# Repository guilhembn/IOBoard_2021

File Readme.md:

# IO board Eurobot 2021

## Protobuf

For the fist time you try to build protobuf files, you need to run `setups.sh` in EmbeddedProto:

`cd software/lib/EmbeddedProto`
`./setup.sh`

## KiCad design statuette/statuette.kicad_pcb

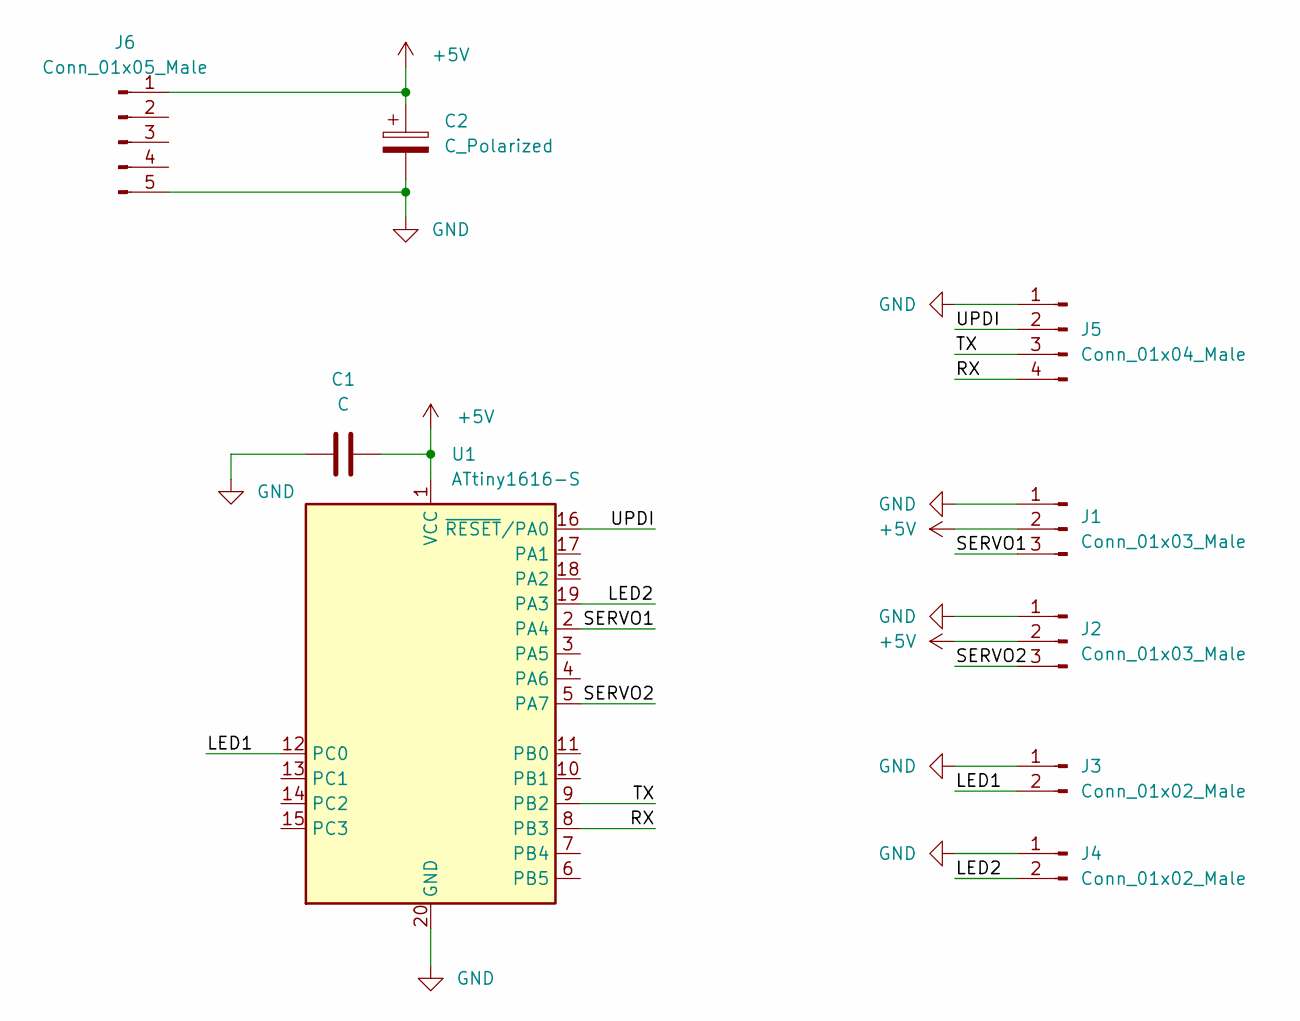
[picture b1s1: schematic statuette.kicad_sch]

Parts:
C1: C; C_0603_1608Metric_Pad1.08x0.95mm_HandSolder
C2: C_Polarized; CP_EIA-6032-28_Kemet-C_Pad2.25x2.35mm_HandSolder
J1, J2: Conn_01x03_Male; PinHeader_1x03_P2.54mm_Vertical
J3, J4: Conn_01x02_Male; PinHeader_1x02_P2.54mm_Vertical
J5: Conn_01x04_Male; Molex_PicoBlade_53047-0410_1x04_P1.25mm_Vertical
J6: Conn_01x05_Male; PinHeader_1x05_P2.54mm_Vertical
U1: ATtiny1616-S; SOIC-20W_7.5x12.8mm_P1.27mm

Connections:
+5V: C1.2, C2.1, J1.2, J2.2, J6.1, U1.1 (VCC)
/LED1: J3.2, U1.12 (PC0)
/LED2: J4.2, U1.19 (PA3)
/RX: J5.4, U1.8 (PB3)
/SERVO1: J1.3, U1.2 (PA4)
/SERVO2: J2.3, U1.5 (PA7)
/TX: J5.3, U1.9 (PB2)
/UPDI: J5.2, U1.16 (~RESET/PA0)
GND: C1.1, C2.2, J1.1, J2.1, J3.1, J4.1, J5.1, J6.5, U1.20 (GND)

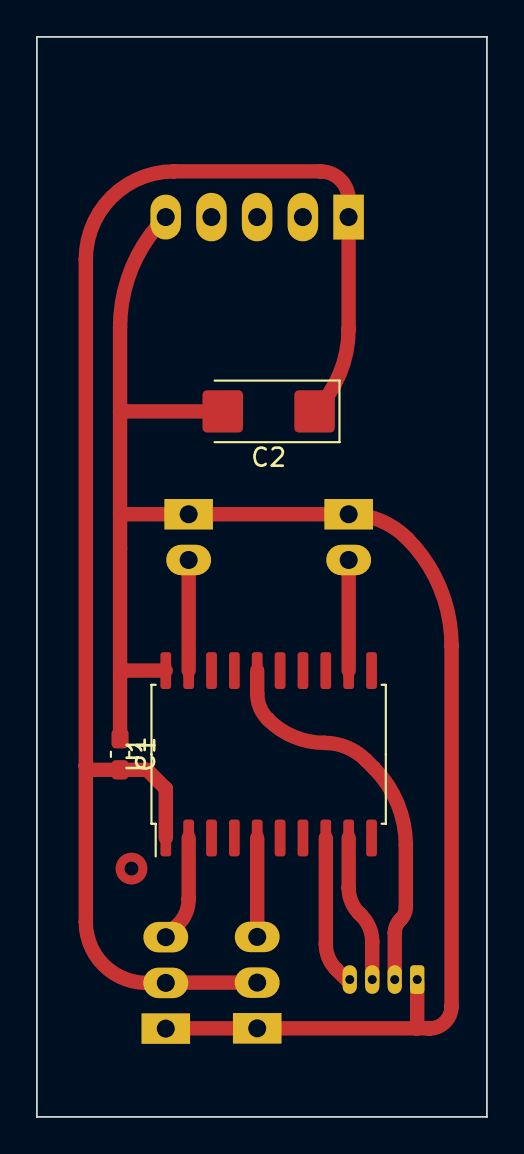
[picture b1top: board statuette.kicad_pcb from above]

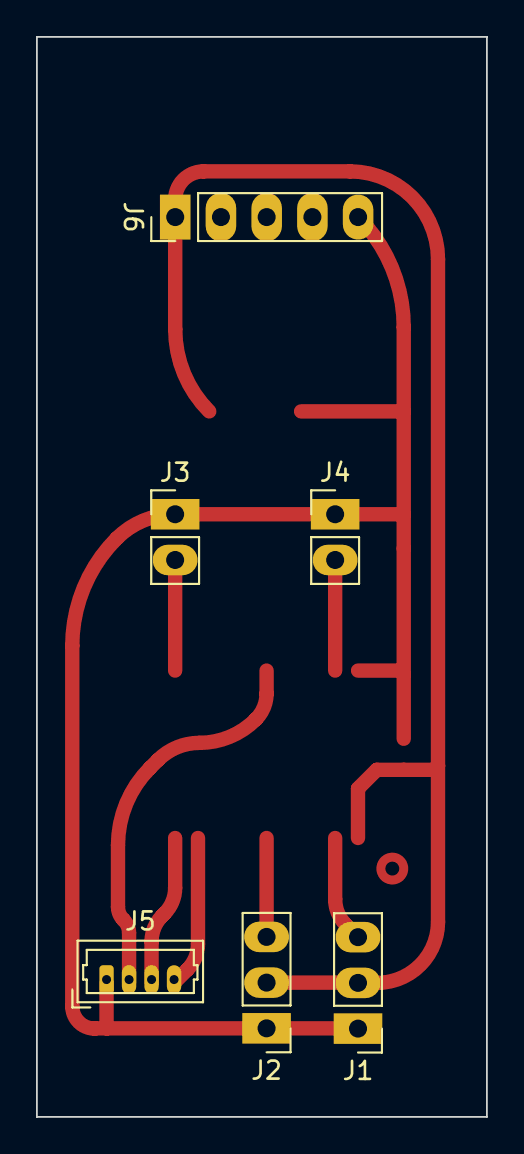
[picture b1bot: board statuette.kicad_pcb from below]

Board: 2 copper layers, 25.0 x 60.0 mm, 9 parts (6 on the bottom side), 9 nets.

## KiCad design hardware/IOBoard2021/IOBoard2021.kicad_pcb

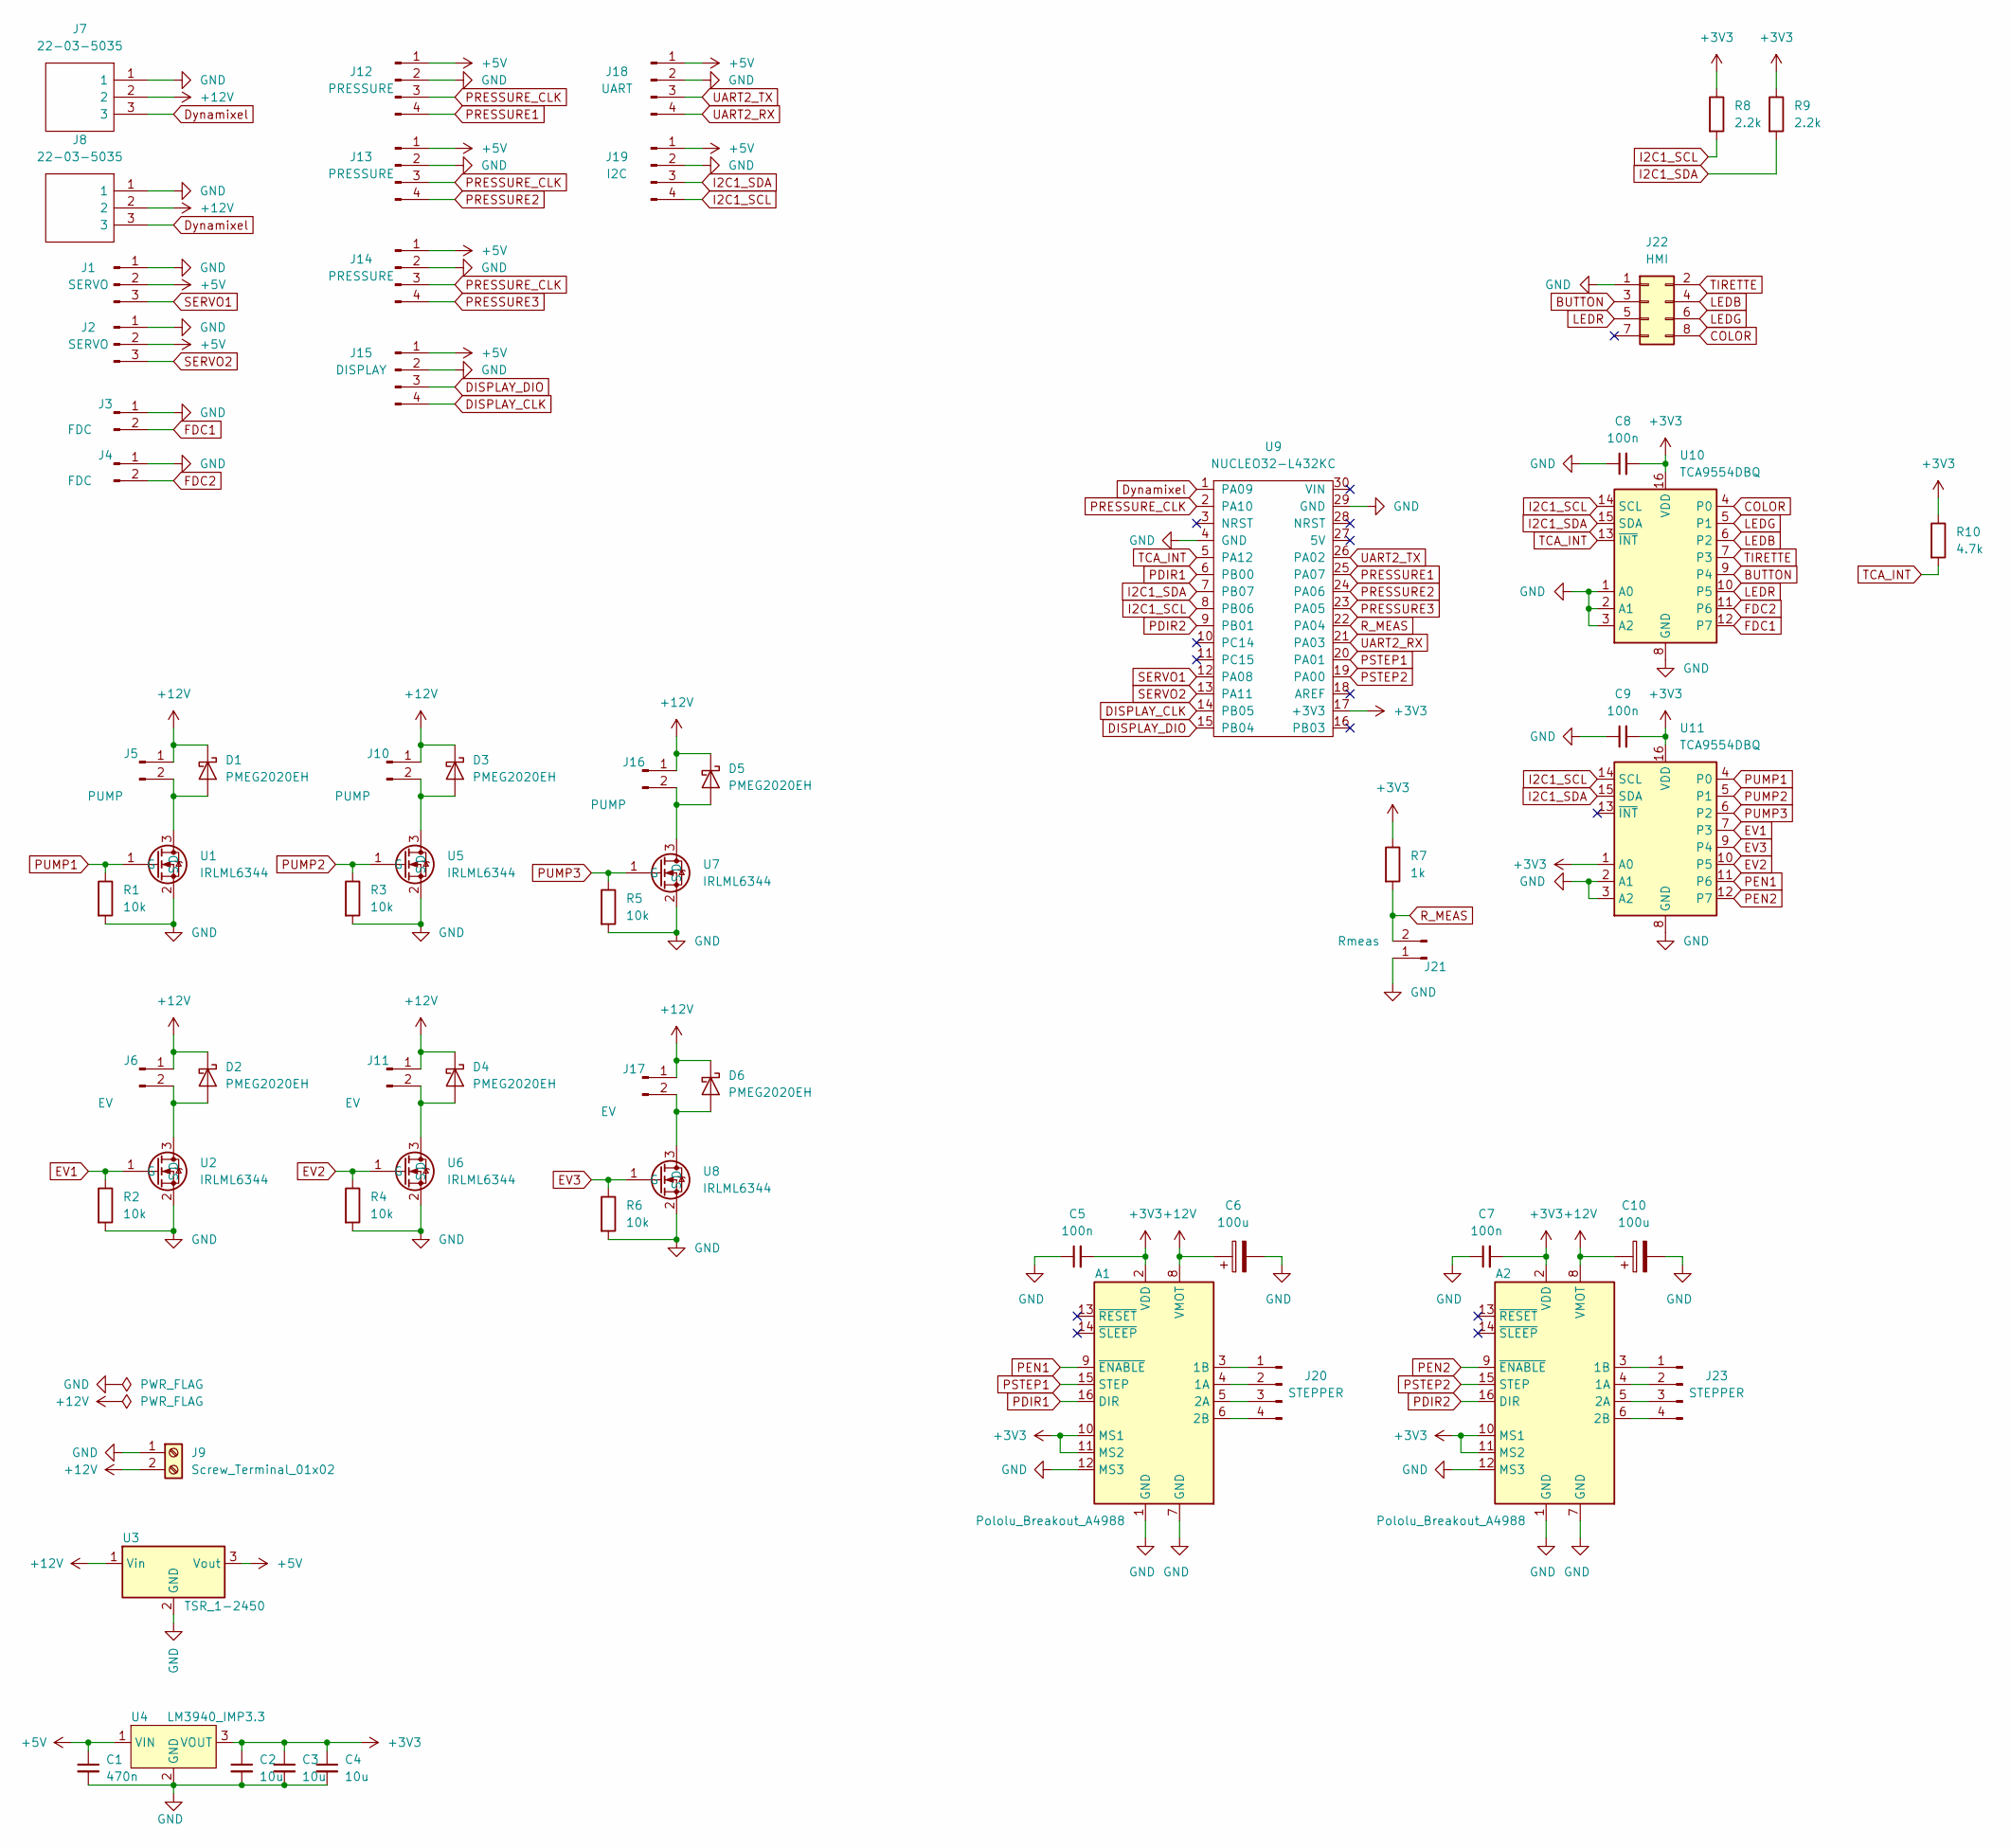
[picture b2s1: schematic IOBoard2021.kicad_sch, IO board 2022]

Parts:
A1, A2: Pololu_Breakout_A4988; Pololu_Breakout-16_15.2x20.3mm
C1: 470n; C_0603_1608Metric_Pad1.08x0.95mm_HandSolder
C2, C3, C4: 10u; C_0603_1608Metric_Pad1.08x0.95mm_HandSolder
C5, C7, C8, C9: 100n; C_0603_1608Metric_Pad1.08x0.95mm_HandSolder
C6, C10: 100u; CP_EIA-7343-31_Kemet-D_Pad2.25x2.55mm_HandSolder
D1, D2, D3, D4, D5, D6: PMEG2020EH; D_SOD-123F
J1, J2: SERVO; PinHeader_1x03_P2.54mm_Vertical
J3, J4: FDC; PinHeader_1x02_P2.54mm_Vertical
J5, J10, J16: PUMP; PinHeader_1x02_P2.54mm_Vertical_SMD_Pin1Left
J6, J11, J17: EV; PinHeader_1x02_P2.54mm_Vertical_SMD_Pin1Left
J7, J8: 22-03-5035; SHDR3W70P0X250_1X3_990X490X590P; Manufacturer_Part_Number 22-03-5035; Mouser Part Number 538-22-03-5035
J9: Screw_Terminal_01x02; TerminalBlock_bornier-2_P5.08mm
J12, J13, J14: PRESSURE; Molex_PicoBlade_53398-0471_1x04-1MP_P1.25mm_Vertical
J15: DISPLAY; Molex_PicoBlade_53398-0471_1x04-1MP_P1.25mm_Vertical
J18: UART; Molex_PicoBlade_53398-0471_1x04-1MP_P1.25mm_Vertical
J19: I2C; Molex_PicoBlade_53398-0471_1x04-1MP_P1.25mm_Vertical
J20, J23: STEPPER; PinHeader_1x04_P2.54mm_Vertical
J21: Rmeas; PinHeader_1x02_P2.54mm_Vertical
J22: HMI; IDC-Header_2x04_P2.54mm_Vertical
R1, R2, R3, R4, R5, R6: 10k; R_0603_1608Metric_Pad0.98x0.95mm_HandSolder
R7: 1k; R_0603_1608Metric_Pad0.98x0.95mm_HandSolder
R8, R9: 2.2k; R_0603_1608Metric_Pad0.98x0.95mm_HandSolder
R10: 4.7k; R_0603_1608Metric_Pad0.98x0.95mm_HandSolder
U1, U2, U5, U6, U7, U8: IRLML6344; SOT-23
U3: TSR_1-2450; Converter_DCDC_TRACO_TSR-1_THT
U4: LM3940_IMP3.3; SOT-223-3_TabPin2
U9: NUCLEO32-L432KC; NUCLEO32
U10, U11: TCA9554DBQ; SSOP-16_3.9x4.9mm_P0.635mm

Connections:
+3V3: A1.2 (VDD), A1.10 (MS1), A1.11 (MS2), A2.2 (VDD), A2.10 (MS1), A2.11 (MS2), C2.1, C3.1, C4.1, C5.2, C7.2, C8.2, C9.2, R7.1, R8.1, R9.1, R10.1, U4.3 (VOUT), U9.17 (+3V3), U10.16 (VDD), U11.1 (A0), U11.16 (VDD)
+5V: C1.1, J1.2, J2.2, J12.1, J13.1, J14.1, J15.1, J18.1, J19.1, U3.3 (Vout), U4.1 (VIN)
+12V: A1.8 (VMOT), A2.8 (VMOT), C6.1, C10.1, D1.1 (K), D2.1 (K), D3.1 (K), D4.1 (K), D5.1 (K), D6.1 (K), J5.1, J6.1, J7.2, J8.2, J9.2, J10.1, J11.1, J16.1, J17.1, U3.1 (Vin)
BUTTON: J22.3, U10.9 (P4)
COLOR: J22.8, U10.4 (P0)
DISPLAY_CLK: J15.4, U9.14 (PB05)
DISPLAY_DIO: J15.3, U9.15 (PB04)
Dynamixel: J7.3, J8.3, U9.1 (PA09)
EV1: R2.1, U2.1 (G), U11.7 (P3)
EV2: R4.1, U6.1 (G), U11.10 (P5)
EV3: R6.1, U8.1 (G), U11.9 (P4)
FDC1: J3.2, U10.12 (P7)
FDC2: J4.2, U10.11 (P6)
GND: A1.1 (GND), A1.7 (GND), A1.12 (MS3), A2.1 (GND), A2.7 (GND), A2.12 (MS3), C1.2, C2.2, C3.2, C4.2, C5.1, C6.2, C7.1, C8.1, C9.1, C10.2, J1.1, J2.1, J3.1, J4.1, J7.1, J8.1, J9.1, J12.2, J13.2, J14.2, J15.2, J18.2, J19.2, J21.1, J22.1, R1.2, R2.2, R3.2, R4.2, R5.2, R6.2, U1.2 (S), U2.2 (S), U3.2 (GND), U4.2 (GND), U5.2 (S), U6.2 (S), U7.2 (S), U8.2 (S), U9.4 (GND), U9.29 (GND), U10.1 (A0), U10.2 (A1), U10.3 (A2), U10.8 (GND), U11.2 (A1), U11.3 (A2), U11.8 (GND)
I2C1_SCL: J19.4, R8.2, U9.8 (PB06), U10.14 (SCL), U11.14 (SCL)
I2C1_SDA: J19.3, R9.2, U9.7 (PB07), U10.15 (SDA), U11.15 (SDA)
LEDB: J22.4, U10.6 (P2)
LEDG: J22.6, U10.5 (P1)
LEDR: J22.5, U10.10 (P5)
unnamed: A1.3 (1B), J20.1
unnamed: A1.4 (1A), J20.2
unnamed: A1.5 (2A), J20.3
unnamed: A1.6 (2B), J20.4
unnamed: A2.3 (1B), J23.1
unnamed: A2.4 (1A), J23.2
unnamed: A2.5 (2A), J23.3
unnamed: A2.6 (2B), J23.4
unnamed: D1.2 (A), J5.2, U1.3 (D)
unnamed: D2.2 (A), J6.2, U2.3 (D)
unnamed: D3.2 (A), J10.2, U5.3 (D)
unnamed: D4.2 (A), J11.2, U6.3 (D)
unnamed: D5.2 (A), J16.2, U7.3 (D)
unnamed: D6.2 (A), J17.2, U8.3 (D)
PDIR1: A1.16 (DIR), U9.6 (PB00)
PDIR2: A2.16 (DIR), U9.9 (PB01)
PEN1: A1.9 (~ENABLE), U11.11 (P6)
PEN2: A2.9 (~ENABLE), U11.12 (P7)
PRESSURE1: J12.4, U9.25 (PA07)
PRESSURE2: J13.4, U9.24 (PA06)
PRESSURE3: J14.4, U9.23 (PA05)
PRESSURE_CLK: J12.3, J13.3, J14.3, U9.2 (PA10)
PSTEP1: A1.15 (STEP), U9.20 (PA01)
PSTEP2: A2.15 (STEP), U9.19 (PA00)
PUMP1: R1.1, U1.1 (G), U11.4 (P0)
PUMP2: R3.1, U5.1 (G), U11.5 (P1)
PUMP3: R5.1, U7.1 (G), U11.6 (P2)
R_MEAS: J21.2, R7.2, U9.22 (PA04)
SERVO1: J1.3, U9.12 (PA08)
SERVO2: J2.3, U9.13 (PA11)
TCA_INT: R10.2, U9.5 (PA12), U10.13 (~INT)
TIRETTE: J22.2, U10.7 (P3)
UART2_RX: J18.4, U9.21 (PA03)
UART2_TX: J18.3, U9.26 (PA02)

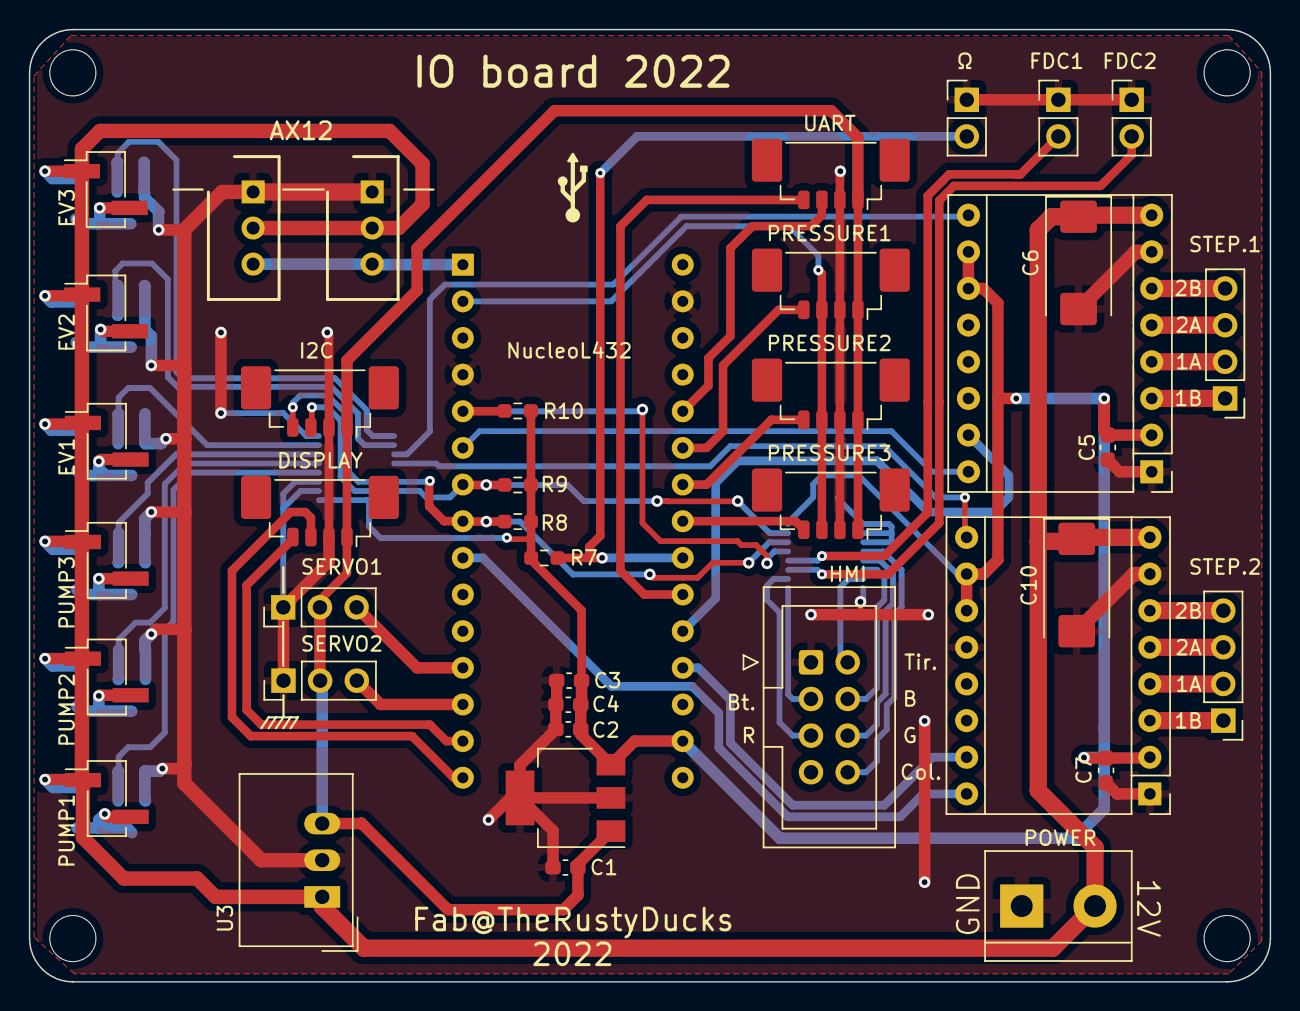
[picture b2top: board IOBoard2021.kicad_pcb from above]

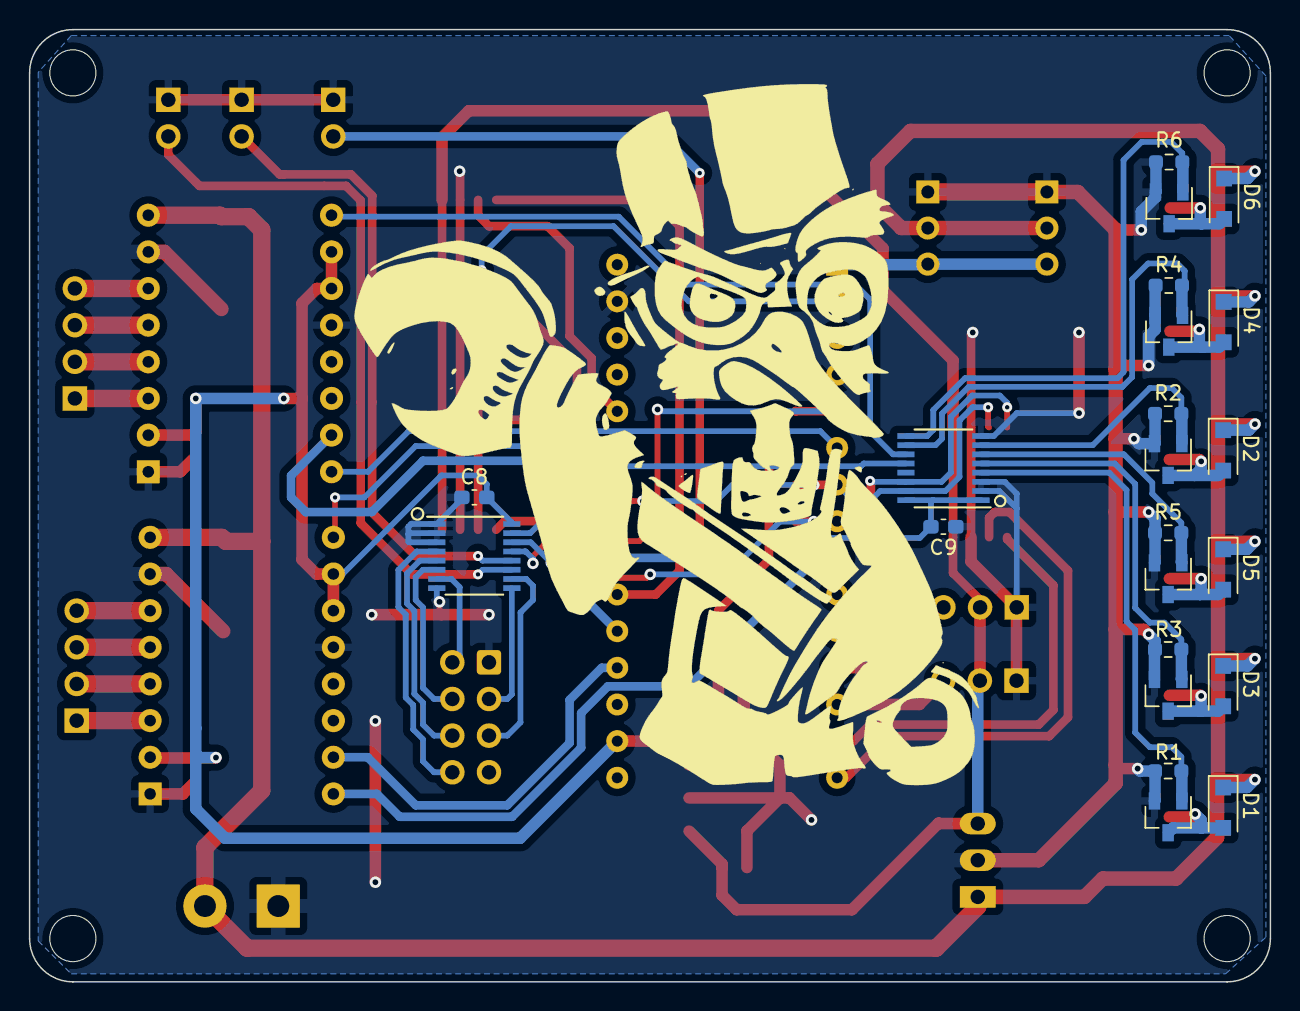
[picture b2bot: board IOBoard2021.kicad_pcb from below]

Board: 2 copper layers, 86.0 x 66.0 mm, 62 parts (22 on the bottom side), 53 nets.

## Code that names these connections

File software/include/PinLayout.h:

#ifndef PINLAYOUT_H
#define PINLAYOUT_H

#include <HardwareSerial.h>
#include <Arduino.h>

constexpr uint32_t ARM1_Z_DRIVER_STEP = PA1;
constexpr uint32_t ARM1_Z_DRIVER_DIR = PB0;
constexpr uint32_t ARM2_Z_DRIVER_STEP = PA0;
constexpr uint32_t ARM2_Z_DRIVER_DIR = PB1;

constexpr uint32_t PRESSURE_CLK = PA10;
constexpr uint32_t PRESSURE_HAT = PA5;
constexpr uint32_t PRESSURE_ARM1 = PA7;
constexpr uint32_t PRESSURE_ARM2 = PA6;

constexpr uint32_t DISPLAY_CLK = PB5;
constexpr uint32_t DISPLAY_DIO = PB4;


constexpr unsigned int ARM1_Z_ROT_DYNAMIXEL_ID = 1;
constexpr unsigned int ARM1_Y_ROT_DYNAMIXEL_ID = 2;
constexpr unsigned int ARM2_Z_ROT_DYNAMIXEL_ID = 3;
constexpr unsigned int ARM2_Y_ROT_DYNAMIXEL_ID = 4;

#define HAT_SERVO1 PA8
#define HAT_SERVO2 PA11

#define UART_TX PA2
#define UART_RX PA3

#define DYNAMIXELS_HALF_DUP_SERIAL Serial1

#define R_MEAS_PIN PA4


#endif /* PINLAYOUT_H */

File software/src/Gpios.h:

#pragma once
#include <Arduino.h>

constexpr uint8_t TCA1_ADDR = 0x20;
constexpr uint8_t TCA2_ADDR = 0x21;
constexpr uint32_t TCA_INT = PA12;

constexpr uint8_t TCA_INPUT_PORT = 0x00;
constexpr uint8_t TCA_OUTPUT_PORT = 0x01;
constexpr uint8_t TCA_POL_INV = 0x02;
constexpr uint8_t TCA_CONFIG = 0x03;

class Gpios {
public:

    enum Signal {
        HAT_VAC_PUMP,
        HAT_VALVE,
        ARM1_VALVE,
        ARM1_VAC_PUMP,
        ARM1_Z_DRIVER_ENABLE,
        ARM1_Z_LIMIT_SWITCH,
        ARM1_Z_DIR,
        ARM1_Z_STEP,
        ARM2_VALVE,
        ARM2_VAC_PUMP,
        ARM2_Z_DRIVER_ENABLE,
        ARM2_Z_LIMIT_SWITCH,
        ARM2_Z_DIR,
        ARM2_Z_STEP,
        PRESSURE_CLK,
        PRESSURE_HAT,
        PRESSURE_ARM1,
        PRESSURE_ARM2,
        DISPLAY_CLK,
        DISPLAY_DIO,
        COLOR,
        TIRETTE,
        LED_R,
        LED_G,
        LED_B,
        BUTTON,
        LED,
    };

    Gpios():tca_interrupt(false){}
    void init();
    
    void setMode(Signal signal, uint32_t mode);
    void write(Signal signal, uint32_t val);
    void toggle(Signal signal);
    int read(Signal signal);

private:
    enum Bank {
        GPIO,
        TCA1,
        TCA2,
    };

    struct PinDef
    {
        Signal signal;
        Bank bank;
        uint32_t pin;
    };
    
    PinDef getDefinition(Signal signal);
    uint8_t tcaConfigure(uint8_t addr, uint8_t config);
    uint8_t tcaWrite(uint8_t addr, uint8_t data);
    void tca1Read();

    bool tca_interrupt;
    uint8_t tca1_state;
    uint8_t tca2_state;
    
    // input=1, output=0
    static constexpr uint8_t TCA1_CONFIG = 0b11011001;
    static constexpr uint8_t TCA2_CONFIG = 0b00000000;

    static constexpr std::array<PinDef, 27> _definitions {{
        {HAT_VAC_PUMP, TCA2, 2},
        {HAT_VALVE, TCA2, 4},
        {ARM1_VALVE, TCA2, 3},
        {ARM1_VAC_PUMP, TCA2, 0},
        {ARM1_Z_DRIVER_ENABLE, TCA2, 6},
        {ARM1_Z_LIMIT_SWITCH, TCA1, 7},
        {ARM1_Z_DIR, GPIO, PB0},
        {ARM1_Z_STEP, GPIO, PA1},
        {ARM2_VALVE, TCA2, 5},
        {ARM2_VAC_PUMP, TCA2, 1},
        {ARM2_Z_DRIVER_ENABLE, TCA2, 7},
        {ARM2_Z_LIMIT_SWITCH, TCA1, 6},
        {ARM2_Z_DIR, GPIO, PB1},
        {ARM2_Z_STEP, GPIO, PA0},
        {PRESSURE_CLK, GPIO, PA10},
        {PRESSURE_HAT, GPIO, PA5},
        {PRESSURE_ARM1, GPIO, PA7},
        {PRESSURE_ARM2, GPIO, PA6},
        {DISPLAY_CLK, GPIO, PB5},
        {DISPLAY_DIO, GPIO, PB4},
        {COLOR, TCA1, 0},
        {TIRETTE, TCA1, 3},
        {LED_R, TCA1, 5},
        {LED_G, TCA1, 1},
        {LED_B, TCA1, 2},
        {BUTTON, TCA1, 4},
        {LED, GPIO, LED_BUILTIN},
    }};


};

extern Gpios gpios;

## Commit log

2021-11-20 Adds submodule EmbeddedProto
2021-11-20 Add protobuf generator script.
2021-11-20 Adds communication
2021-11-21 Updates parameters
2021-11-21 Improves interfaces to Arm, Hat and Vacuum System
2021-11-21 Updates platformio.ini to flash the IO board
2021-11-21 Updates communication to new ducklink messages
2021-11-21 Updates main
2021-12-15 Use TeensyStep instead of AccelStep.
2021-12-15 Make hat translation smooth.
2021-12-15 Automatically disable steppers after timeout.
2021-12-15 Add ProcedureManager and ProcStack.
2021-12-15 Limit AX12 speed.
2021-12-16 Procedure return status.
2021-12-16 Add TurnStack procedure.
2021-12-23 Start elec
2022-02-01 Finish schematic and copper layout.
2022-02-01 Finish board.
2022-02-01 Add schematic PDF.
2022-02-09 Add statuette elec.
2022-02-12 Adapt to new board.
2022-02-12 Add driver for pressure readings.
2022-02-12 Add display.
2022-02-13 Add arm2.
2022-03-24 Add Home procedure.
2022-03-24 Send error messages.
2022-03-25 Handle HMI messages.
2022-03-28 Fix procedures.
2022-03-29 Set timeouts for procedures.
2022-03-29 hmi small fix.
2022-03-29 Add procedure Unstack, and fix various bugs.
2022-03-29 adjust parameters.
2022-04-26 Enable UART RX pin.
2022-04-26 Cleaning.
2022-04-26 Do not move arms at startup.
2022-05-20 offset for Y dynamixels
2022-05-20 turn stack proc go lower
2022-05-24 Fix Y offset.
2022-05-24 Disable stepper timeout
2022-05-24 [stack] wait a bit during stack
2022-05-24 Add RUNNING_FREE procedure state.
2022-05-24 Add HalfUnstack procedure
2022-05-24 Proc unstack param use.
2022-05-24 Open valve when starting pump.
2022-06-27 Make procedure safer.
